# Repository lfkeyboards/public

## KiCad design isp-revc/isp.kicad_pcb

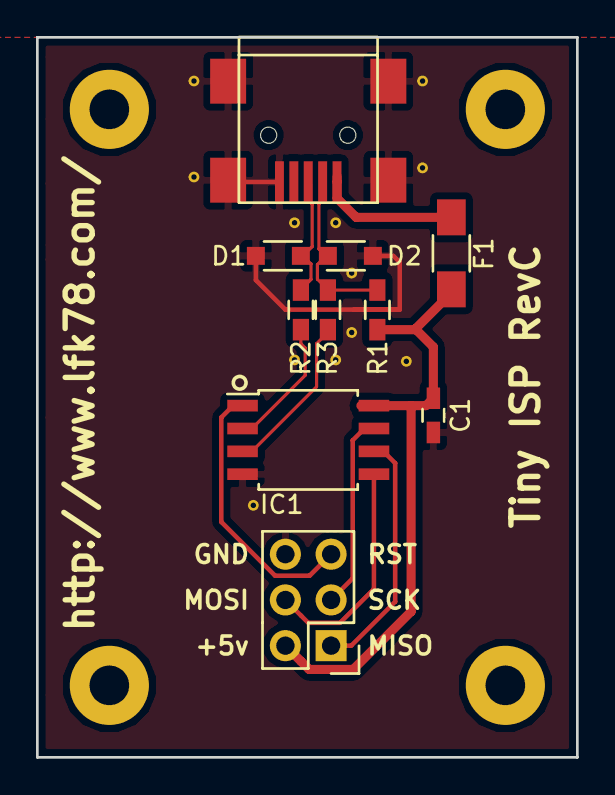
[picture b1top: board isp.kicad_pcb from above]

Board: 2 copper layers, 30.0 x 40.0 mm, 10 parts (0 on the bottom side), 11 nets.

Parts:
C1: 0.1µF; C_0603_HandSoldering
D1, D2: 3.6v; SOD-323_HandSoldering
F1: F_Small; C_1206_HandSoldering
IC1: ATTINY45-S; SOIJ-8_5.3x5.3mm_Pitch1.27mm
P1: USB_OTG; USB_Mini-B
P2: CONN_02X03; Pin_Header_Straight_2x03
R1: 1.7kΩ; R_0603_HandSoldering
R2, R3: 68Ω; R_0603_HandSoldering

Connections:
+5V: C1.1, F1.1, IC1.8, P2.2, R1.1
D+: D1.1, P1.3, R2.2
D-: D2.1, P1.2, R1.2, R3.2
GND: C1.2, D1.2, D2.2, IC1.4, P1.5, P1.6, P2.6
MISO: IC1.6, P2.1
MOSI: IC1.5, P2.4
unnamed: F1.2, P1.1
unnamed: IC1.2, R2.1
unnamed: IC1.3, R3.1
RST: IC1.1, P2.5
SCK: IC1.7, P2.3
